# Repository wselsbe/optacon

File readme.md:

# Optacon

This project aims to recreate the [Optacon](https://en.wikipedia.org/wiki/Optacon) (OPtical to TActile CONverter), a reading aid for the blind. The user moves a small camera module over a document to scan one letter at a time. The main module has a "tactile display": a 6x24 array of vibrating pins, so the user can feel the shape of the letter being scanned with their fingertip.

The vibrating pins are actuated by piezoelectric bimorphs, similar to those used in refreshable braille displays. The Optacon uses vibrating pins instead of static, and achieves a higher pin density: 1mm x 2mm versus 2.5mm x 2.5mm.
The following videos show the display in action. The piezo bimorphs actuate at around 250Hz, the motion appears slowed down by a stroboscopic led.

The high density tactile display remains state of the art. Even now, 50 years later, there is no technology available that achieves the same high density while still remaining portable and battery powered.

# Recreating the tactile display
The smallest commercially available piezoelectric actuators are those meant for braille cells, and are 2.5mm wide. No piezo manufacturer wanted to try to create narrower actuators.

My solution is to start with an off the shelf 40mm x 20mm x 0.9mm actuator, and dice it into 20 individual parallel actuators with a [wafer dicing saw](https://www.eevblog.com/forum/reviews/micro-automation-m1006-dicing-saw). This uses a very precise air bearing spindle with a very thin (55 micron) diamond blade to cut through the piezoceramic. Because the blade is water cooled, the piezoceramic actuator remains below the curie temperature (about 150°C) and does not lose its polarisation.

## Holding and mounting the piezoceramic actuator for dicing
Holding the actuators during and after dicing proved challenging. Typically silicon wafers are mounted with [UV dicing tape](https://www.adwill-global.com/en/tape/dicing-d.html), but this tape is expensive.
Another potential solution is [heat release tape](https://www.nitto.com/eu/en/products/e_parts/electronic001/), where the adhesive softens at higher temperature (but still below the piezoceramic curie temperature), but this is similarly expensive.

I got some success by using [Crystalbond 509](https://www.aremco.com/mounting-adhesives/): by heating it to 74°C on a hotplate I could apply the adhesive to a glass disc, add the piezoceramic, and letting the adhesive cool down to harden. The disc is then held in place the the dicing saw's vacuum chuck. But transferring the diced actuators to a pcb, while still remaining parallel after dicing, proved to be too difficult. The Crystalbond 509 has to be released by using heat and a solvent (acetone), without affecting the second adhesive used to attach the piezoceramic reeds to the pcb.

The key proved to be in reversing the steps.

1. First populate the pcb and reflow solder as usual
2. Apply the conductive adhesive on the pcb actuator pads with a stencil. I'm using MG Chemicals [8331S](https://mgchemicals.com/products/adhesives/electrically-conductive-adhesives/electrically-conductive-paste/) 2-part or [9410](https://mgchemicals.com/products/adhesives/electrically-conductive-adhesives/conductive-adhesive/) 1-part silver epoxy.
3. Attach the piezoceramic and heat-cure the epoxy on a hot plate or in a reflow (toaster) oven. The above epoxies can cure below the curie temperature.
4. Mount the pcb to the glass disc with [Crystalbond 555-HMP](https://www.aremco.com/mounting-adhesives/). Although 555 has much lower tensile strength compared to 509, the larger surface area of the pcb is enough to keep it in place.
   The silver epoxy provides enough shear strengths to hold the individual actuators on one end. By applying the Crystalbond 555 on the underside of the piezoceramic through the slots in the pcb, the free ends of the diced piezoceramic reeds remain supported.
5. Dice the piezoceramic.
6. Crystalbond 555 is water soluble, any adhesive exposed to the water cooling from the dicing blade will be removed quickly while dicing. To detach the pcb from the glass disc it can be placed in a heated ultrasonic cleaner.

# Electronics

## Actuator board

The actuator board is designed around 2 components: a high voltage piezo driver, and high voltage shift registers .
All components are chosen for small size and low height, to keep the boards stackable. The tallest component is the inductor at 1.2mm. The passive components are 0603 for manual pick and place.

### Piezo Driver

The [TI DRV2665](https://www.ti.com/product/DRV2665) can output 100V with only an inductor and capacitor. It has an I2C interface and an analog input. 
Alternatives are [DRV2667](https://www.ti.com/product/DRV2667) (pin compatible) and [DRV8667](https://www.ti.com/product/DR8667) & [DRV2700](https://www.ti.com/product/DRV2700) (analog only)
The inductor [TDK VLS3012HBX-3R3M](https://product.tdk.com/en/search/inductor/inductor/smd/info?part_no=VLS3012HBX-3R3M) is chosen for low height, low resistance (150mΩ), and high current (2.37A temp rating).
The capacitor is rated for 200V.
TI has an [excel sheet](https://www.ti.com/tool/download/SLOR113) to help calculate the values for the inductor, capacitor, and feedback resistors.

To increase the efficiency the piezo driver is powered from VIN (battery or usb). The I2C lines are pulled up to VDD (3.3V), compatible down to 1.8V

The piezo driver has a differential output, which can drive piezos at 200V peak to peak. Because of the shift registers only one output (up to 100V) is used.
Without input the outputs float at half the boost voltage, ideally the external controller should make sure the input is pulled down.

The I2C and analog input pins are broken out to the FFC connector.

### Shift Registers

The [Microchip HV509](https://www.microchip.com/en-us/product/HV509) high voltage shift registers are used to address the individual piezo actuators. There are no real alternatives available in QFN or similar low height package.
The common BP pin is connected to the common bottom & top electrodes on the piezos. The individual outputs go to the center electrodes. There are 16 outputs per shift registers, 10 are used on each shift register, the other 6 are unused.
Diode D1 is needed to bias the output transistors to at least VDD before the high voltage is enabled.
The datasheet says the minimum voltage is 50V for the outputs to switch. In practice this does not look like a major issue: if the HV is a sine wave they might switch late, but will still pass through the lower voltage after switching. (Needs further testing)

Both shift registers are chained together, the SPI pins (clock, data in, data out) and Latch and Polarity are broken out to the FFC connector

## Motherboard

The motherboard is designed to drive several actuator boards (up to 6), a future revision will accept external input such as a camera to read printed letters.
It's based on an ESP32-S3-WROOM-1 module.
Currently the goal of the motherboard is to act as a controller and interface to the actuator boards. At first, the firmware should simply generate a sinewave and step through the individual actuators, as a test for the actuator boards.

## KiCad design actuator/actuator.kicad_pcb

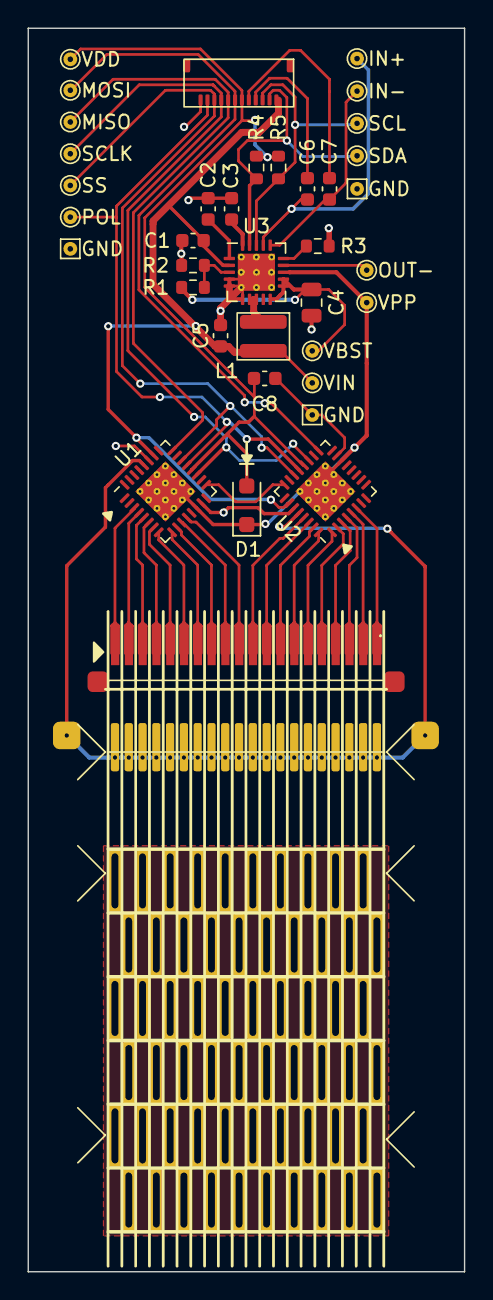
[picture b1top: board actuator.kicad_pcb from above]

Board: 2 copper layers, 31.7 x 90.2 mm, 38 parts (0 on the bottom side), 44 nets.

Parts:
C1: 1 µF; C_0603_1608Metric
C2, C3, C6, C7, C8: 0.1 µF; C_0603_1608Metric
C4: 0.1 µF 150V+; C_0805_2012Metric
C5: 10 µF; C_0603_1608Metric
D1: D; D_SOD-123F
J1: Conn_01x12; Hirose_FH34SRJ-12S-0.5SH
J2: Conn_01x40_Socket; Hirose_FH34SRJ-40S-0.5SH
L1: 3.3 µH; TDK_VLS_3012
R1: 549k; R_0603_1608Metric
R2, R3: 6.98k; R_0603_1608Metric
R4, R5: 3.3k; R_0603_1608Metric
TP1, TP15: VDD; TestPoint_THTPad_D1.0mm_Drill0.5mm
TP2, TP2#2, TP2#3: TestPoint; TestPoint_THTPad_1.0x1.0mm_Drill0.5mm
TP3, TP4, TP5, TP6, TP7, TP8, TP9, TP10, TP11, TP12, TP13, TP14: TestPoint; TestPoint_THTPad_D1.0mm_Drill0.5mm
U1, U2: HV509; HVQFN-32-1EP_5x5mm_P0.5mm_EP3.1x3.1mm_ThermalVias
U3: DRV2665; Texas_S-PVQFN-N20_EP2.7x2.7mm_ThermalVias
piezo1: Conn_01x22; piezox20

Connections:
/IN+: C6.2, J1.9
/IN-: C7.1, J1.8
/MISO: J1.5, TP9.1, U1.24 (DOUT)
/MOSI: J1.6, TP8.1, U2.17 (DIN)
/OUT-: TP5.1, U3.14 (OUT-)
/POL: J1.2, TP13.1, U1.21 (~POL~), U2.21 (~POL~)
/PZT_Common: U1.28 (BP), U2.28 (BP), piezo1.21
/SCL: J1.10, R5.1, TP11.1, U3.18 (SCL)
/SCLK: J1.4, TP12.1, U1.19 (CLK), U2.19 (CLK)
/SDA: J1.11, R4.2, TP10.1, U3.19 (SDA)
/SS: J1.3, TP14.1, U1.22 (~LE~), U2.22 (~LE~)
/VBST: C4.1, R1.1, TP4.1, U3.10 (VBST), U3.11 (VBST), U3.12 (PVDD)
/VDD: C8.1, D1.2 (A), J1.7, R4.1, R5.2, TP1.1, U1.20 (VDD), U2.20 (VDD)
/VIN: C1.1, C5.1, J1.12, L1.2, TP15.1, U1.26 (VBIAS), U2.26 (VBIAS), U3.2 (VDD)
/VPP: D1.1 (K), TP3.1, U1.14 (VPP), U1.33 (VPP), U2.14 (VPP), U2.33 (VPP), U3.13 (OUT+)
/reed1: J2.39, J2.40, U1.3 (HVout10)
/reed2: J2.37, J2.38, U1.4 (HVout9)
/reed3: J2.35, J2.36, U1.5 (HVout8)
/reed4: J2.33, J2.34, U1.6 (HVout7)
/reed5: J2.31, J2.32, U1.7 (HVout6)
/reed6: J2.29, J2.30, U1.8 (HVout5)
/reed7: J2.27, J2.28, U1.9 (HVout4)
/reed8: J2.25, J2.26, U1.10 (HVout3)
/reed9: J2.23, J2.24, U1.11 (HVout2)
/reed10: J2.21, J2.22, U1.12 (HVout1)
/reed11: J2.19, J2.20, U2.29 (HVout16)
/reed12: J2.17, J2.18, U2.30 (HVout15)
/reed13: J2.15, J2.16, U2.31 (HVout14)
/reed14: J2.13, J2.14, U2.32 (HVout13)
/reed15: J2.11, J2.12, U2.1 (HVout12)
/reed16: J2.9, J2.10, U2.2 (HVout11)
/reed17: J2.7, J2.8, U2.3 (HVout10)
/reed18: J2.5, J2.6, U2.4 (HVout9)
/reed19: J2.3, J2.4, U2.5 (HVout8)
/reed20: J2.1, J2.2, U2.6 (HVout7)
GND: C1.2, C2.2, C3.2, C4.2, C5.2, C8.2, J1.1, R2.1, R3.2, TP2.1, TP2#2.1, TP2#3.1, U1.15 (GND), U1.27 (HVGND), U2.15 (GND), U2.27 (HVGND), U3.4 (GND), U3.5 (GND), U3.6 (GND), U3.21 (GND)
unnamed: L1.1, U3.7 (SW), U3.8 (SW)
unnamed: U1.17 (DIN), U2.24 (DOUT)
unnamed: R1.2, R2.2, U3.3 (FB)
unnamed: C6.1, TP6.1, U3.17 (IN+)
unnamed: C7.2, TP7.1, U3.16 (IN-)
unnamed: C3.1, U3.20 (REG)
unnamed: R3.1, U3.15 (REXT)
unnamed: C2.1, U3.1 (VPUMP)

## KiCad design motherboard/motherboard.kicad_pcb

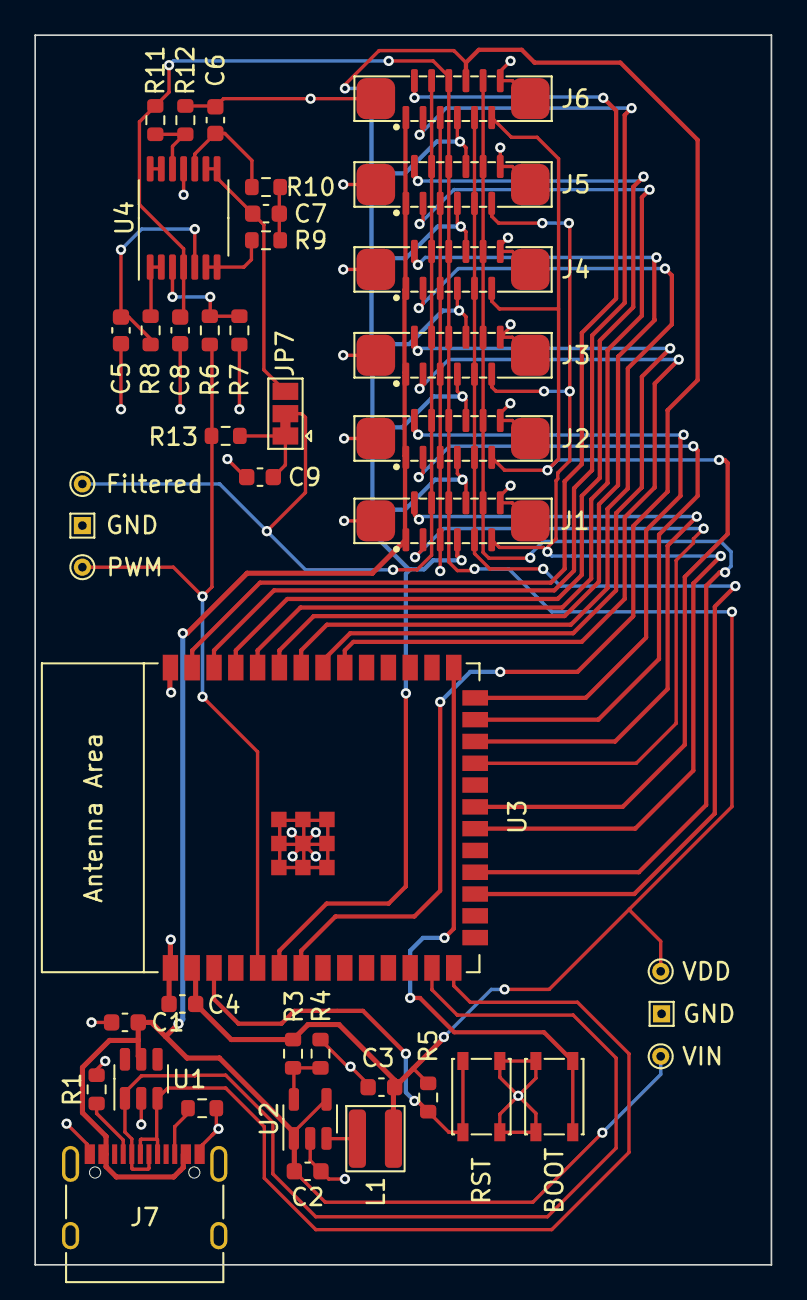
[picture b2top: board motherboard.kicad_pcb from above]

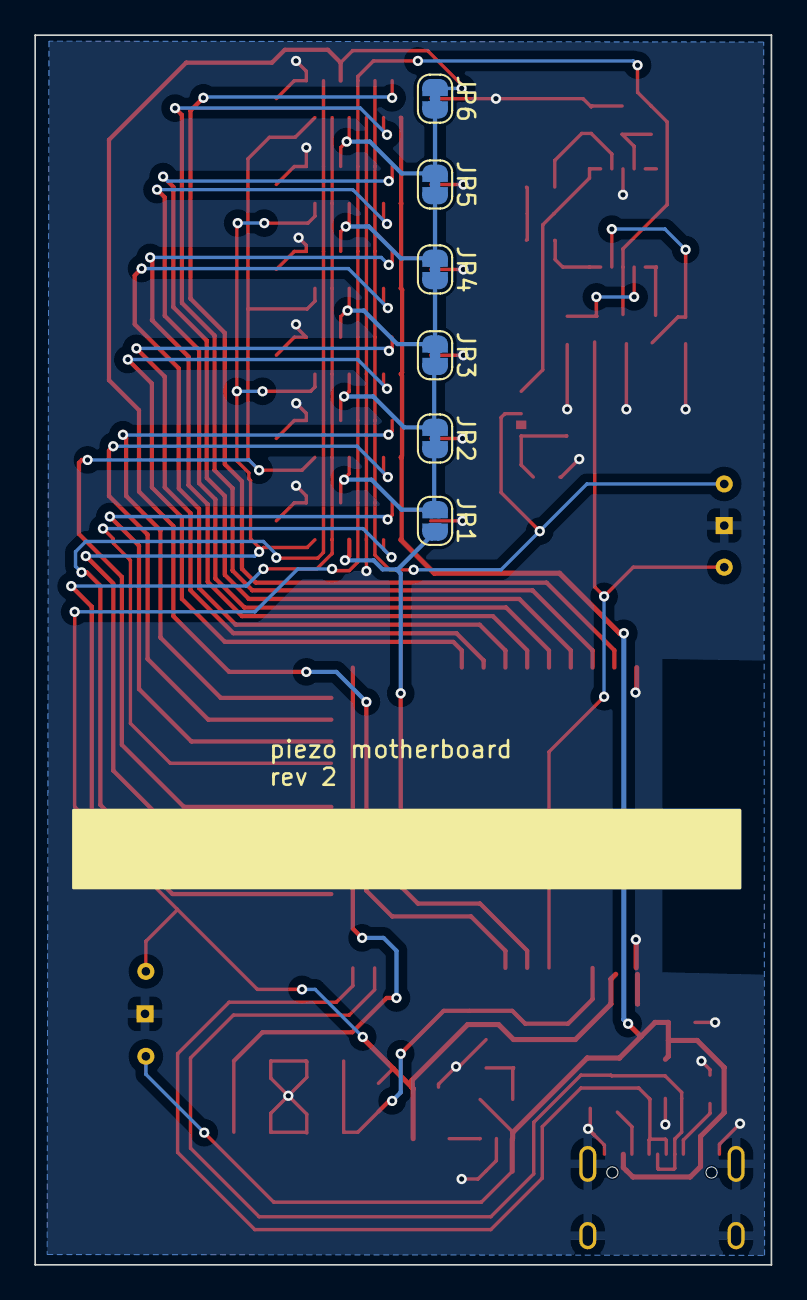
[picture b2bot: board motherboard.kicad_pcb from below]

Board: 2 copper layers, 42.9 x 71.7 mm, 49 parts (6 on the bottom side), 46 nets.

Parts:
C1, C4: C; C_0603_1608Metric
C2: 4.7µF; C_0603_1608Metric
C3: 10µF; C_0603_1608Metric
C5, C6, C8: 0.01µF; C_0603_1608Metric
C7: 0.047µF; C_0603_1608Metric
C9: 0.1µF; C_0603_1608Metric
J1, J2, J3, J4, J5, J6: Conn_01x12_MountingPin; Jushuo_AFC11-S12I
J7: USB_C_Receptacle_USB2.0; USB_C_Receptacle_XKB_U262-16XN-4BVC11
JP1: SolderJumper_2_Open; SolderJumper-2_P1.3mm_Open_RoundedPad1.0x1.5mm
JP2, JP3, JP4, JP5, JP6: SolderJumper_2_Bridged; SolderJumper-2_P1.3mm_Bridged_RoundedPad1.0x1.5mm
JP7: SolderJumper_3_Bridged12; SolderJumper-3_P1.3mm_Bridged12_Pad1.0x1.5mm
L1: 3.3µH; TDK_VLS_3012
R1, R2: 5.1K; R_0603_1608Metric
R3: 31.6k; R_0603_1608Metric
R4: 6.98k; R_0603_1608Metric
R5: R; R_0603_1608Metric
R6: 12.4K; R_0603_1608Metric
R7: 6.19K; R_0603_1608Metric
R8: 4.02K; R_0603_1608Metric
R9: 1.21K; R_0603_1608Metric
R10: 2.74K; R_0603_1608Metric
R11, R12: 100K; R_0603_1608Metric
R13: 390; R_0603_1608Metric
SW1: RST; SW_SPST_PTS810
SW2: BOOT; SW_SPST_PTS810
TP1, TP2, TP4, TP6: TestPoint; TestPoint_THTPad_D1.0mm_Drill0.5mm
TP3, TP5: TestPoint; TestPoint_THTPad_1.0x1.0mm_Drill0.5mm
U1: SRV05-4; SOT-23-6
U2: M3406-ADJ; SOT-23-5
U3: ESP32-S3-WROOM-1
U4: LM324; TSSOP-14_4.4x5mm_P0.65mm

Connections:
/D+: J7.A6 (D+), J7.B6 (D+), U1.3 (IO2), U3.14 (GPIO20/U1CTS/ADC2_CH9/CLK_OUT1/USB_D+)
/D-: J7.A7 (D-), J7.B7 (D-), U1.1 (IO1), U3.13 (GPIO19/U1RTS/ADC2_CH8/CLK_OUT2/USB_D-)
/IN+: J1.4, J2.4, J3.4, J4.4, J5.4, J6.4, JP7.2 (C), TP2.1
/MISO1: J1.8, J2.7, JP1.1 (A), JP2.2 (B)
/MISO2: J2.8, J3.7, JP2.1 (A), JP3.2 (B)
/MISO3: J3.8, J4.7, JP3.1 (A), JP4.2 (B)
/MISO4: J4.8, J5.7, JP4.1 (A), JP5.2 (B)
/MISO5: J5.8, J6.7, JP5.1 (A), JP6.2 (B)
/MISO6: J6.8, JP6.1 (A), U3.7 (GPIO7/TOUCH7/ADC1_CH6)
/MOSI1: J1.7, JP1.2 (B), U3.6 (GPIO6/TOUCH6/ADC1_CH5)
/POL1: J1.11, J3.11, J5.11, U3.20 (GPIO12/TOUCH12/ADC2_CH1/FSPICLK/FSPIIO6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)
/POL2: J2.11, J4.11, J6.11, U3.21 (GPIO13/TOUCH13/ADC2_CH2/FSPIQ/FSPIIO7/S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)
/PWM_OUT: R6.1, R13.1, TP1.1, U3.5 (GPIO5/TOUCH5/ADC1_CH4)
/SCL1: J1.3, U3.23 (GPIO21)
/SCL2: J2.3, U3.25 (GPIO48/SPICLK_N/SUBSPICLK_N_DIFF)
/SCL3: J3.3, U3.32 (MTCK/GPIO39/CLK_OUT3/SUBSPICS1)
/SCL4: J4.3, U3.34 (MTDI/GPIO41/CLK_OUT1)
/SCL5: J5.3, U3.36 (U0RXD/GPIO44/CLK_OUT2)
/SCL6: J6.3, U3.38 (GPIO2/TOUCH2/ADC1_CH1)
/SCLK: J1.9, J2.9, J3.9, J4.9, J5.9, J6.9, U3.17 (GPIO9/TOUCH9/ADC1_CH8/FSPIHD/SUBSPIHD)
/SDA1: J1.2, U3.24 (GPIO47/SPICLK_P/SUBSPICLK_P_DIFF)
/SDA2: J2.2, U3.26 (GPIO45)
/SDA3: J3.2, U3.33 (MTDO/GPIO40/CLK_OUT2)
/SDA4: J4.2, U3.35 (MTMS/GPIO42)
/SDA5: J5.2, U3.37 (U0TXD/GPIO43/CLK_OUT1)
/SDA6: J6.2, U3.39 (GPIO1/TOUCH1/ADC1_CH0)
/SS: J1.10, J2.10, J3.10, J4.10, J5.10, J6.10, U3.18 (GPIO10/TOUCH10/ADC1_CH9/FSPICS0/FSPIIO4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)
/VDD: C3.1, C4.1, C8.1, J1.6, J2.6, J3.6, J4.6, J5.6, J6.6, L1.2, R3.2, R5.1, R11.1, TP6.1, U3.2 (3V3), U4.4 (V+)
/VIN: C1.2, C2.1, J1.1, J2.1, J3.1, J4.1, J5.1, J6.1, J7.A4 (VBUS), J7.A9 (VBUS), J7.B4 (VBUS), J7.B9 (VBUS), TP4.1, U1.5 (VP), U2.1 (RUN), U2.4 (VIN)
GND: C1.1, C2.2, C3.2, C4.2, C5.2, C6.1, C8.2, C9.2, J1.5, J1.12, J1.MP (MountPin), J2.5, J2.12, J2.MP (MountPin), J3.5, J3.12, J3.MP (MountPin), J4.5, J4.12, J4.MP (MountPin), J5.5, J5.12, J5.MP (MountPin), J6.5, J6.12, J6.MP (MountPin), J7.A1 (GND), J7.A12 (GND), J7.B1 (GND), J7.B12 (GND), J7.S1 (SHIELD), R1.2, R2.2, R4.1, R7.2, R12.2, SW1.1, SW2.1, TP3.1, TP5.1, U1.2 (VN), U2.2 (GND), U3.1 (GND), U3.40 (GND), U3.41 (GND), U4.11 (V-)
unnamed: C7.1, R9.2, R10.1
unnamed: J7.A5 (CC1), R1.1
unnamed: J7.B5 (CC2), R2.1
unnamed: C9.1, JP7.1 (A), R13.2
unnamed: C7.2, JP7.3 (B), U4.8, U4.9 (-)
unnamed: R3.1, R4.2, U2.5 (FB)
unnamed: L1.1, U2.3 (SW)
unnamed: R5.2, SW1.2, U3.3 (EN)
unnamed: SW2.2, U3.27 (GPIO0/BOOT)
unnamed: R6.2, R7.1, U4.3 (+)
unnamed: R8.1, U4.1, U4.2 (-)
unnamed: C5.1, R8.2, U4.5 (+)
unnamed: R9.1, U4.6 (-), U4.7
unnamed: C6.2, R10.2, U4.10 (+)
unnamed: R11.2, R12.1, U4.12 (+)
unnamed: U4.13 (-), U4.14

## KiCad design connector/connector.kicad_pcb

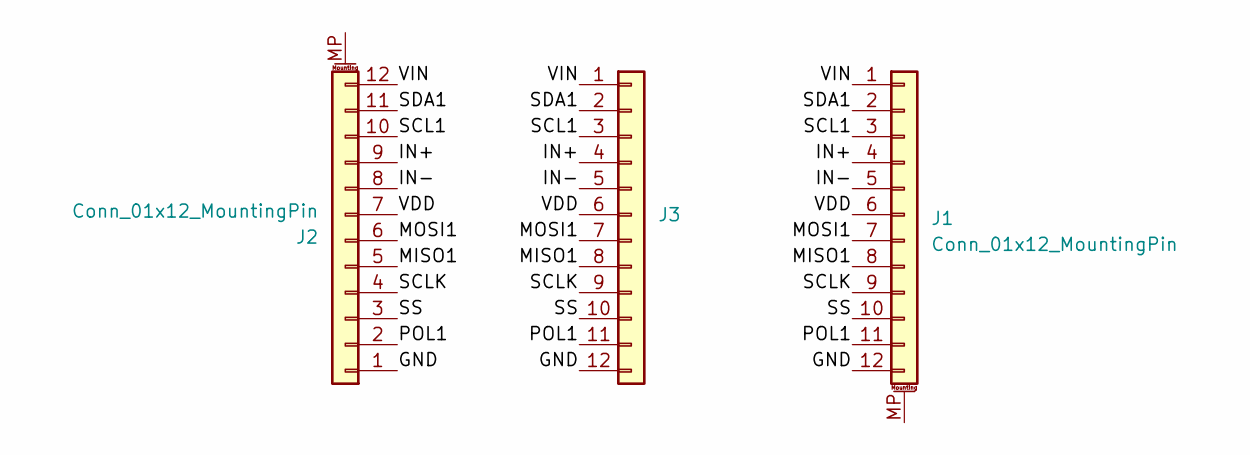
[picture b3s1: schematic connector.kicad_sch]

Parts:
J1, J2: Conn_01x12_MountingPin; Hirose_FH34SRJ-12S-0.5SH
J3: Conn_01x12; PinHeader_1x12_P2.54mm_Vertical

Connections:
/GND: J1.12, J2.1, J3.12
/IN+: J1.4, J2.9, J3.4
/IN-: J1.5, J2.8, J3.5
/MISO1: J1.8, J2.5, J3.8
/MOSI1: J1.7, J2.6, J3.7
/POL1: J1.11, J2.2, J3.11
/SCL1: J1.3, J2.10, J3.3
/SCLK: J1.9, J2.4, J3.9
/SDA1: J1.2, J2.11, J3.2
/SS: J1.10, J2.3, J3.10
/VDD: J1.6, J2.7, J3.6
/VIN: J1.1, J2.12, J3.1

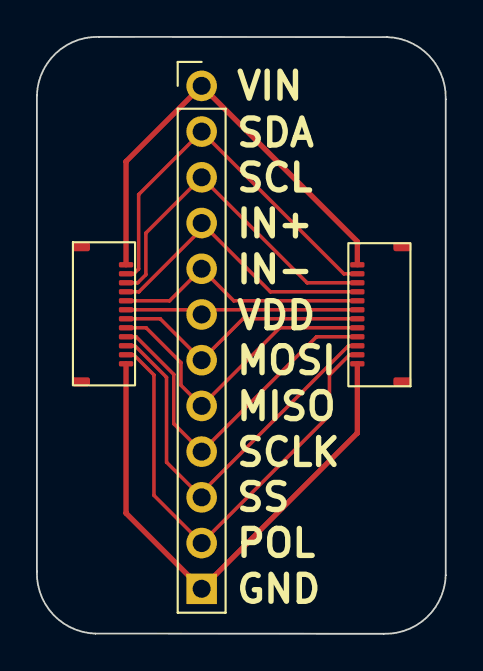
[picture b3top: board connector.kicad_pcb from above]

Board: 2 copper layers, 22.7 x 33.2 mm, 3 parts (0 on the bottom side), 12 nets.

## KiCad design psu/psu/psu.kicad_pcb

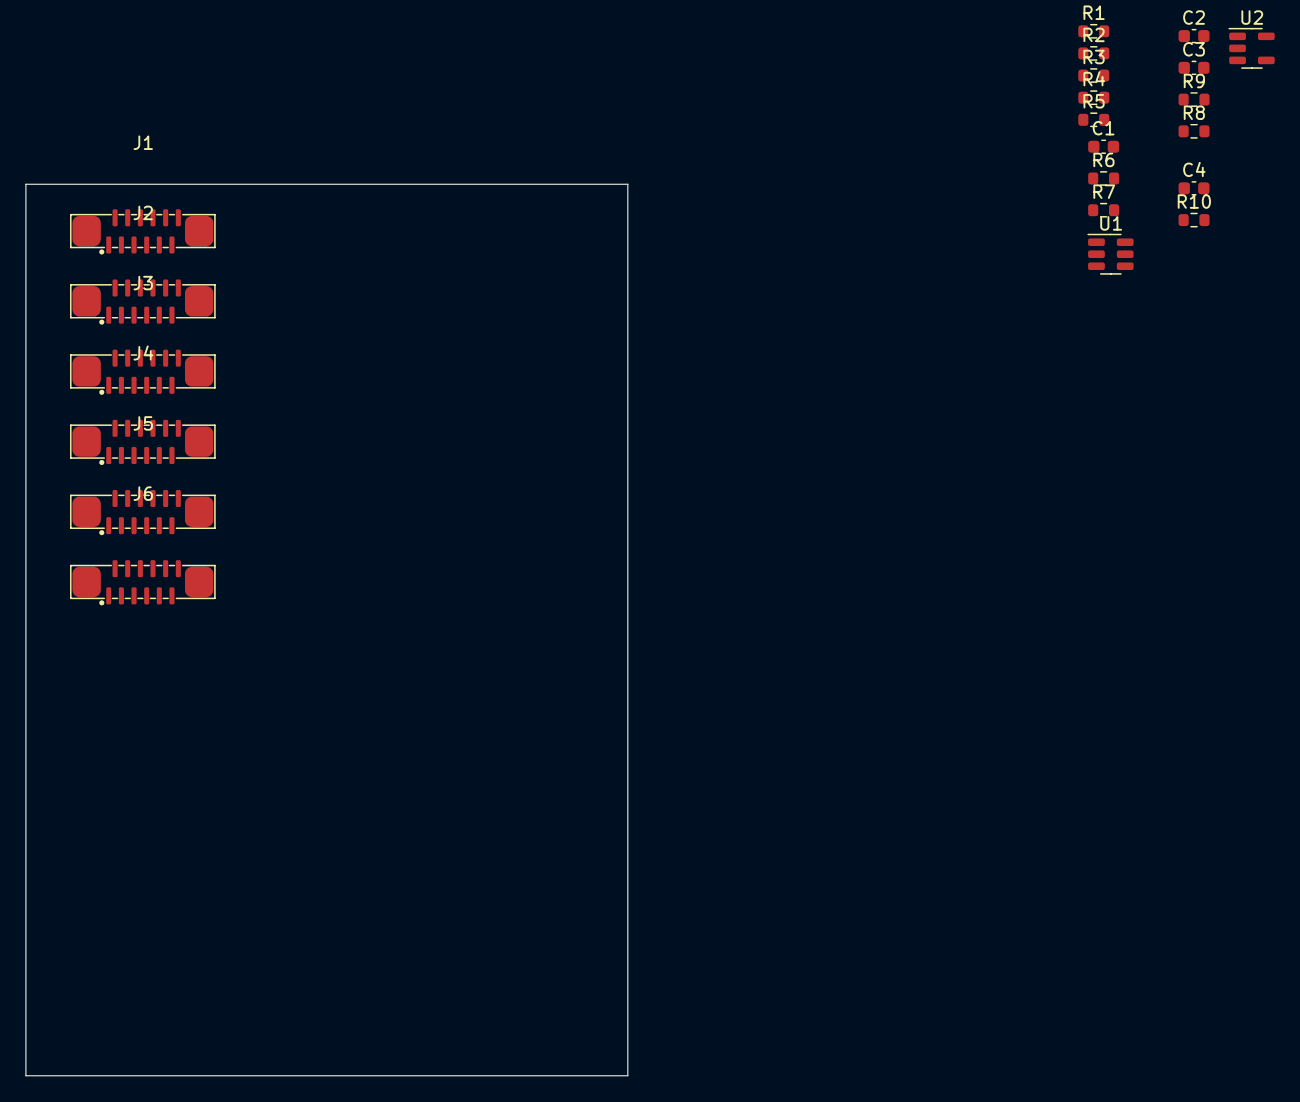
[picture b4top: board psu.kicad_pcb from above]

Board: 2 copper layers, 47.6 x 70.5 mm, 22 parts (0 on the bottom side), 21 nets, no tracks yet.

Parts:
C1, C4: C; C_0603_1608Metric
C2: 4.7µF; C_0603_1608Metric
C3: 10µF; C_0603_1608Metric
J1, J2, J3, J4, J5, J6: Conn_01x12; Jushuo_AFC11-S12I
R1, R2, R3, R4, R5: 0; R_0603_1608Metric
R6, R7: 5.1K; R_0603_1608Metric
R8: 31.6k; R_0603_1608Metric
R9: 6.98k; R_0603_1608Metric
R10: R; R_0603_1608Metric
U1: SRV05-4; SOT-23-6
U2: M3406-ADJ; SOT-23-5

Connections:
/IN+: J1.4, J2.4, J3.4, J4.4, J5.4, J6.4
/IN-: J1.5, J2.5, J3.5, J4.5, J5.5, J6.5
/MISO1: J1.8, R1.1
/MISO2: J2.8, R2.1
/MISO3: J3.8, R3.1
/MISO4: J4.8, R4.1
/MISO5: J5.8, R5.1
/MOSI2: J2.7, R1.2
/MOSI3: J3.7, R2.2
/MOSI4: J4.7, R3.2
/MOSI5: J5.7, R4.2
/MOSI6: J6.7, R5.2
/POL1: J1.11, J3.11, J5.11
/POL2: J2.11, J4.11, J6.11
/SCLK: J1.9, J2.9, J3.9, J4.9, J5.9, J6.9
/SS: J1.10, J2.10, J3.10, J4.10, J5.10, J6.10
/VDD: C3.1, C4.1, J1.6, J2.6, J3.6, J4.6, J5.6, J6.6, R8.2, R10.1
/VIN: C2.1, J1.1, J2.1, J3.1, J4.1, J5.1, J6.1, U2.1 (RUN), U2.4 (VIN)
/Vusb: C1.2, U1.5 (VP)
GND: C1.1, C2.2, C3.2, C4.2, J1.12, J2.12, J3.12, J4.12, J5.12, J6.12, R6.2, R7.2, R9.1, U1.2 (VN), U2.2 (GND)
unnamed: R8.1, R9.2, U2.5 (FB)

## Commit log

2022-04-19 driver pcb v1
2022-04-20 wip: piezo footprint, drv2665 symbol
2022-04-20 drv2665 subsheet
2022-04-25 schematic, footprints
2022-06-08 bom update
2022-06-13 driver board
2022-06-15 cleanup
2022-06-15 hole pattern for piezo vacuum
2022-06-16 gerbers
2022-06-16 no paste (stencil) for piezo individual pads
2022-08-21 WIP -added clearance for reeds center conductor header pins -removed jumper resistor & output cap on VBST -changed C4 high voltage cap to 0805, lower height above board -added C5 10µF cap at inductor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
2022-08-21 add test points, mounting holes
2022-08-21 hierarchical sheet for shift registers
2022-11-02 move vias out of pad ; fix ground plane under hv528
2022-11-05 thermal vias for HV509/HV528
2022-11-07 test points
2022-11-08 align test points
2022-11-15 pcb + stencils ordered from pcbgogo
2023-06-11 remove VBIAS, EN, REG rename & reorder nets for i2c, spi add IN- next to IN+ (AIN) add SMD FPC connector for piezo use BP instead of HVOUTs for piezo_common
2023-06-12 J2 (mounting) pads no paste
2023-06-13 separate VIN and VDD
2023-06-13 realign test points
2023-06-13 remove fp-info-cache (added to gitignore)
2023-06-13 move SDA trace around R4, R5
2023-06-25 work in progress: reorder project files
2023-06-25 wip: move files, common symbols+footprints
2023-06-27 motherboard basics routed
2023-06-27 reroute motherboard: no traces under antenna
2023-06-28 fpc connector mounting points
2023-07-03 actuator: add capacitor for vdd, no exposed copper on backside
2023-07-03 connector: breakout board for 12-pin fpc
2023-07-03 motherboard: buttons silkscreen
2023-07-03 export: pcbs + stencils ordered from pcbgogo
2023-07-17 actuator ibom
2023-08-01 move piezo smd connector, rework pads & adhesive
2023-08-01 Quick relayout of motherboard - rotate ESP32, move supporting parts to bottom edge, reroute traces
2023-08-02 rev3.1 gerbers
2023-10-24 restore slots under actuators (fix #5)
2023-10-24 move up ffc connector (fix #1)
2023-10-29 add initial readme
2024-01-22 motherboard low pass filter
2024-01-22 actuator move testpoints to subsheets
2024-01-28 motherboard add test points
2024-01-28 add 1st order low pass filter, with solder jumper
2024-01-28 add/update revision texts
